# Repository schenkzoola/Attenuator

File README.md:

<picture>
  <source media="(prefers-color-scheme: dark)" srcset="docs/images/logo-light.png">
  
</picture>

# Levels

A 3HP Eurorack dual passive attenuator from **Schenktronics**. It has two channels, each with an input, an output and a level knob. The second input is normalled to the first, so one signal can be sent out at two different levels. It needs no power.

## Features

- 3HP Eurorack, 15 mm deep, and it needs no power
- Two channels, each turning a signal down from full level to off
- In 2 is normalled to In 1: one input, two outputs at independent levels
- Works on audio, CV, gates and bipolar signals
- The whole kit is through-hole, with 22 solder joints

## Documentation

| Document | For | PDF |
|----------|-----|-----|
| [User Manual](docs/manual.md) | Using the module | [PDF](docs/pdf/levels-manual.pdf) |
| [Assembly Guide](docs/assembly-guide.md) | Building the kit | [PDF](docs/pdf/levels-assembly-guide.pdf) |
| [Bill of Materials](docs/BOM.md) ([CSV](docs/BOM.csv)) | Parts and sourcing | |

## Repository layout

```
hardware/
  levels/                      Main PCB (KiCad 5.1 schematic, KiCad 10 PCB)
    Levels.sch                   Schematic
    Levels.kicad_pcb             PCB layout
    Levels.step                  3D model
    BOM.ods                      Original BOM spreadsheet
  panel/                       Faceplate (KiCad 10, made as an aluminium PCB)
    LevelsFaceplate.kicad_pcb    Faceplate layout
manufacturing/
  levels/                      Gerbers and drill files for the main PCB
  panel/                       Gerbers, drill files and the panel drawing (.dxf)
docs/                         Manual, assembly guide, BOM, images
  drawings/                     Scripts that generate the drawings
  pdf/                          PDF versions and their build settings
```

## Fabrication

| Board | Size | Layers | Thickness | Notes |
|-------|------|--------|-----------|-------|
| Main PCB | 15 × 100 mm | 2 | 1.6 mm | Standard green is fine |
| Faceplate | 15 × 128.5 mm | 1 | 1.6 mm | Aluminium PCB, white solder mask, black silkscreen. Only the front copper layer is used, so FR4 works too. |

Upload the matching `*Gerbers.zip` to any common PCB fab.

## License

This hardware design and its documentation are licensed under [CC BY-NC-SA 4.0](https://creativecommons.org/licenses/by-nc-sa/4.0/). See [LICENSE](LICENSE).

The Schenktronics name and logo are trademarks of Nathan Schenk and are not covered by the CC BY-NC-SA 4.0 license.

## Links

- Tindie: <https://www.tindie.com/products/schenktronics/passive-attenuator/>
- ModularGrid: <https://modulargrid.net/e/schenktronics-atten>
- Build video: <https://www.youtube.com/watch?v=RKkGsIigaSM>
- Website: <https://schenktronics.com>

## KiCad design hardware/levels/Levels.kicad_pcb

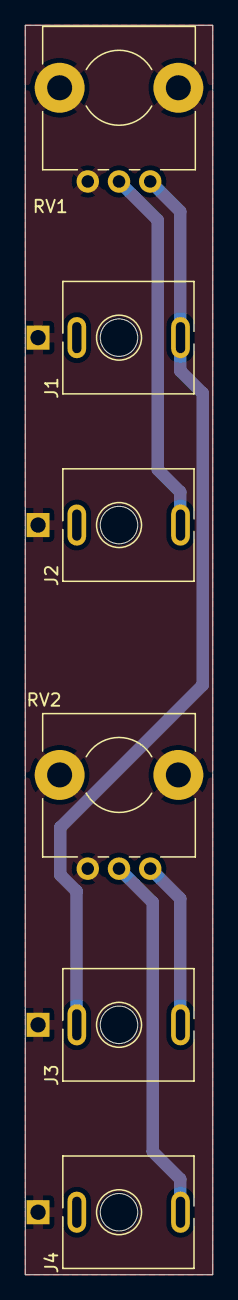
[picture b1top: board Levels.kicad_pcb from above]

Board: 2 copper layers, 15.0 x 100.0 mm, 6 parts (0 on the bottom side), 5 nets.

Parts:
J1, J2, J3, J4: AudioJack2_SwitchT; Jack_3.5mm_QingPu_WQP-PJ398SM_Vertical_CenterHole_OvalPads
RV1, RV2: R_POT; Potentiometer_Alps_RK09L_Plated_Mount_Holes

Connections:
GND: J1.S, J2.S, J3.S, J4.S, RV1.3, RV2.3
unnamed: J1.T, J3.TN, RV1.1
unnamed: J2.T, RV1.2
unnamed: J3.T, RV2.1
unnamed: J4.T, RV2.2

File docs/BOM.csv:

Qty,Reference,Description,Manufacturer,Part Number,Link
4,J1-J4,"3.5mm mono switched jack, vertical, with nut (J3 must be switched)",QingPu,WQP-PJ398SM or WQP518MA,http://www.qingpu-electronics.com/en/products/WQP-PJ398SM-362.html
2,"RV1, RV2","Potentiometer, 100k linear, 9mm, vertical PCB mount with board-lock lugs, 15mm D shaft, with nut (or equivalent)",TT Electronics/BI,P0915N-FC15BR100K,https://www.digikey.com/product-detail/en/tt-electronics-bi/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
2,,"Knob, skirted, 15mm, fits pot shaft and covers nut (or equivalent)",Davies Molding,1227-J,https://www.digikey.com/product-detail/en/davies-molding-llc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
1,,"Main PCB, 15x100mm, 2-layer, 1.6mm",Schenktronics,Levels v1.0,
1,,"Faceplate, 3HP, 1.6mm aluminium PCB",Schenktronics,Levels Faceplate,

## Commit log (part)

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2019-11-25 Moved potentiometers to top.
    Add top layer gnd pour
2019-11-25 Add BOM
2019-11-26 Generate gerbers and step
2019-11-27 Move jacks to center
2019-11-27 Add faceplate .dxf
2019-11-28 Create Faceplate pcb
2019-11-28 Finish faceplate, add gerbers
2019-12-04 Update lower two jack holes in faceplate.
